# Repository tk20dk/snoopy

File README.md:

# snoopy
Three phase power meter

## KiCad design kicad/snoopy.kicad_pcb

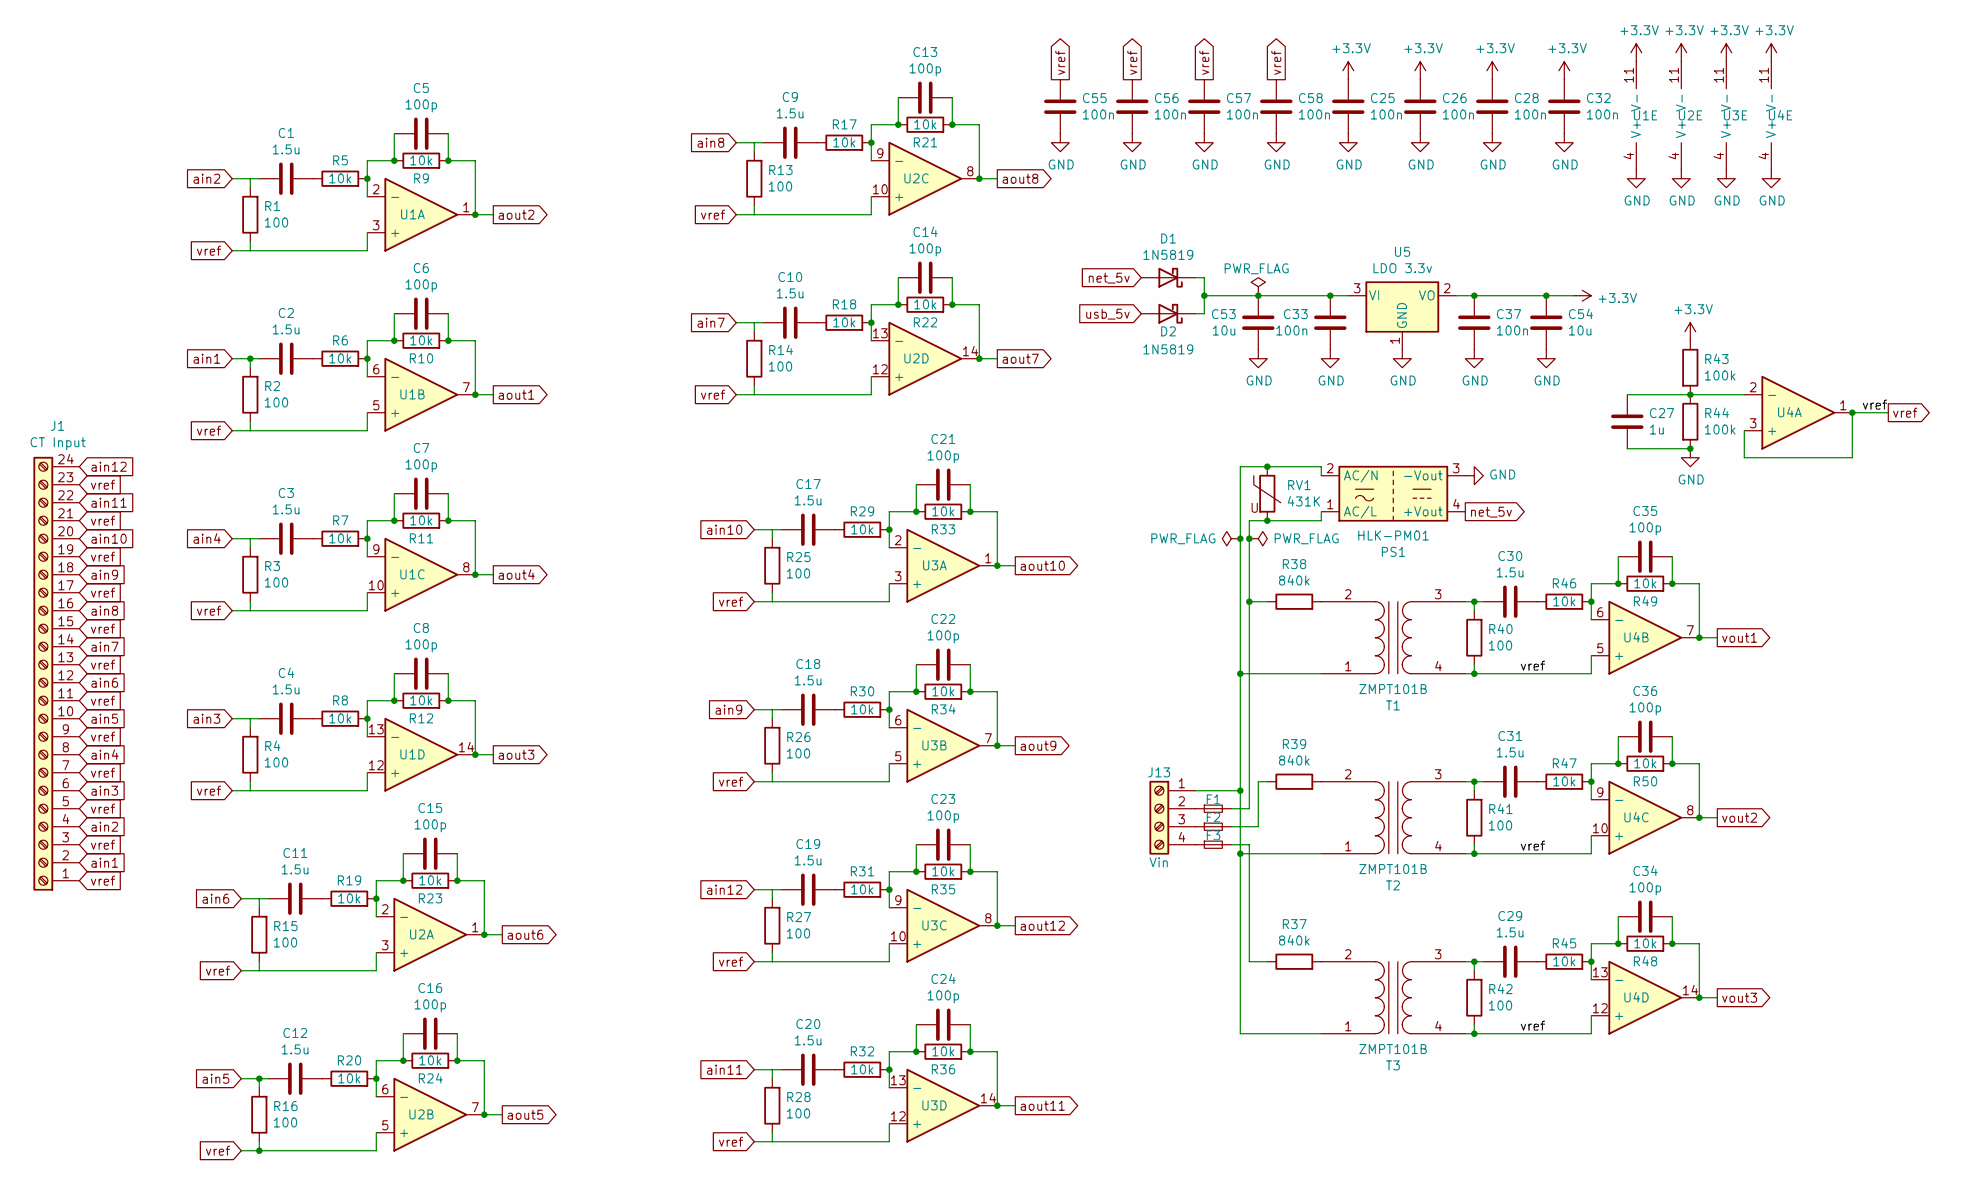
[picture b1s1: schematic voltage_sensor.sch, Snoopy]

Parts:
C1, C2, C3, C4, C9, C10, C11, C12, C17, C18, C19, C20, C29, C30, C31: 1.5u; C_0603_1608Metric
C5, C6, C7, C8, C13, C14, C15, C16, C21, C22, C23, C24, C34, C35, C36: 100p; C_0603_1608Metric
C25, C26, C28, C32, C33, C37, C55, C56, C57, C58: 100n; C_0603_1608Metric
C27: 1u; C_0603_1608Metric
C53, C54: 10u; C_0805_2012Metric
D1, D2: 1N5819; D_0805_2012Metric
F1, F2, F3: 500mA; Fuse_1206_3216Metric
J1: CT Input; TerminalBlock_1x24_P2.54mm_Horizontal
J13: Vin; TerminalBlock_bornier-4_P5.08mm
PS1: HLK-PM01; Converter_ACDC_HiLink_HLK-PMxx
R1, R2, R3, R4, R13, R14, R15, R16, R25, R26, R27, R28, R40, R41, R42: 100; R_0805_2012Metric
R5, R6, R7, R8, R9, R10, R11, R12, R17, R18, R19, R20, R21, R22, R23, R24, R29, R30, R31, R32, R33, R34, R35, R36, R45, R46, R47, R48, R49, R50: 10k; R_0603_1608Metric
R37, R38, R39: 840k; R_0805_2012Metric
R43, R44: 100k; R_0603_1608Metric
RV1: 431K; RV_Disc_D7mm_W3.7mm_P5mm
T1, T2, T3: ZMPT101B; Transformer_ZAPT101B
U1, U2, U3, U4: MCP604; SOIC-14_3.9x8.7mm_P1.27mm
U5: LDO 3.3v; SOT-223-3_TabPin2

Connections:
+3V3: C25.1, C26.1, C28.1, C32.1, C37.1, C54.1, R43.1, U1.11 (V-), U2.11 (V-), U3.11 (V-), U4.11 (V-), U5.2 (VO); also elsewhere on the board
GND: C25.2, C26.2, C27.2, C28.2, C32.2, C33.1, C37.2, C53.1, C54.2, C55.2, C56.2, C57.2, C58.2, PS1.3 (-Vout), R44.2, U1.4 (V+), U2.4 (V+), U3.4 (V+), U4.4 (V+), U5.1 (GND); also elsewhere on the board
unnamed: C1.2, R5.1
unnamed: C2.2, R6.1
unnamed: C3.2, R7.1
unnamed: C4.2, R8.1
unnamed: C5.2, R5.2, R9.1, U1.2 (-)
unnamed: C6.2, R6.2, R10.1, U1.6 (-)
unnamed: C7.2, R7.2, R11.1, U1.9 (-)
unnamed: C8.2, R8.2, R12.1, U1.13 (-)
unnamed: C9.2, R17.1
unnamed: C10.2, R18.1
unnamed: C11.2, R19.1
unnamed: C12.2, R20.1
unnamed: C13.2, R17.2, R21.1, U2.9 (-)
unnamed: C14.2, R18.2, R22.1, U2.13 (-)
unnamed: C15.2, R19.2, R23.1, U2.2 (-)
unnamed: C16.2, R20.2, R24.1, U2.6 (-)
unnamed: C17.2, R29.1
unnamed: C18.2, R30.1
unnamed: C19.2, R31.1
unnamed: C20.2, R32.1
unnamed: C21.2, R29.2, R33.1, U3.2 (-)
unnamed: C22.2, R30.2, R34.1, U3.6 (-)
unnamed: C23.2, R31.2, R35.1, U3.9 (-)
unnamed: C24.2, R32.2, R36.1, U3.13 (-)
unnamed: C27.1, R43.2, R44.1, U4.2 (-)
unnamed: C29.1, R42.2, T3.3 (SA)
unnamed: C29.2, R45.1
unnamed: C30.1, R40.2, T1.3 (SA)
unnamed: C30.2, R46.1
unnamed: C31.1, R41.2, T2.3 (SA)
unnamed: C31.2, R47.1
unnamed: C33.2, C53.2, D1.1 (K), D2.1 (K), U5.3 (VI)
unnamed: C34.2, R45.2, R48.1, U4.13 (-)
unnamed: C35.2, R46.2, R49.1, U4.6 (-)
unnamed: C36.2, R47.2, R50.1, U4.9 (-)
unnamed: F1.1, J13.2
unnamed: F1.2, PS1.1 (AC/L), R38.1, RV1.2
unnamed: F2.1, J13.3
unnamed: F2.2, R39.1
unnamed: F3.1, J13.4
unnamed: F3.2, R37.1
unnamed: J13.1, PS1.2 (AC/N), RV1.1, T1.1 (AA), T2.1 (AA), T3.1 (AA)
unnamed: R37.2, T3.2 (AB)
unnamed: R38.2, T1.2 (AB)
unnamed: R39.2, T2.2 (AB)
ain1: C2.1, J1.2, R2.2
ain2: C1.1, J1.4, R1.2
ain3: C4.1, J1.6, R4.2
ain4: C3.1, J1.8, R3.2
ain5: C12.1, J1.10, R16.2
ain6: C11.1, J1.12, R15.2
ain7: C10.1, J1.14, R14.2
ain8: C9.1, J1.16, R13.2
ain9: C18.1, J1.18, R26.2
ain10: C17.1, J1.20, R25.2
ain11: C20.1, J1.22, R28.2
ain12: C19.1, J1.24, R27.2
aout1: C6.1, R10.2, U1.7; also elsewhere on the board
aout2: C5.1, R9.2, U1.1; also elsewhere on the board
aout3: C8.1, R12.2, U1.14; also elsewhere on the board
aout4: C7.1, R11.2, U1.8; also elsewhere on the board
aout5: C16.1, R24.2, U2.7; also elsewhere on the board
aout6: C15.1, R23.2, U2.1; also elsewhere on the board
aout7: C14.1, R22.2, U2.14; also elsewhere on the board
aout8: C13.1, R21.2, U2.8; also elsewhere on the board
aout9: C22.1, R34.2, U3.7; also elsewhere on the board
aout10: C21.1, R33.2, U3.1; also elsewhere on the board
aout11: C24.1, R36.2, U3.14; also elsewhere on the board
aout12: C23.1, R35.2, U3.8; also elsewhere on the board
net_5v: D1.2 (A), PS1.4 (+Vout)
usb_5v: D2.2 (A); also elsewhere on the board
vout1: C35.1, R49.2, U4.7; also elsewhere on the board
vout2: C36.1, R50.2, U4.8; also elsewhere on the board
vout3: C34.1, R48.2, U4.14; also elsewhere on the board
vref: C55.1, C56.1, C57.1, C58.1, J1.1, J1.3, J1.5, J1.7, J1.9, J1.11, J1.13, J1.15, J1.17, J1.19, J1.21, J1.23, R1.1, R2.1, R3.1, R4.1, R13.1, R14.1, R15.1, R16.1, R25.1, R26.1, R27.1, R28.1, R40.1, R41.1, R42.1, T1.4 (SB), T2.4 (SB), T3.4 (SB), U1.3 (+), U1.5 (+), U1.10 (+), U1.12 (+), U2.3 (+), U2.5 (+), U2.10 (+), U2.12 (+), U3.3 (+), U3.5 (+), U3.10 (+), U3.12 (+), U4.1, U4.3 (+), U4.5 (+), U4.10 (+), U4.12 (+); also elsewhere on the board

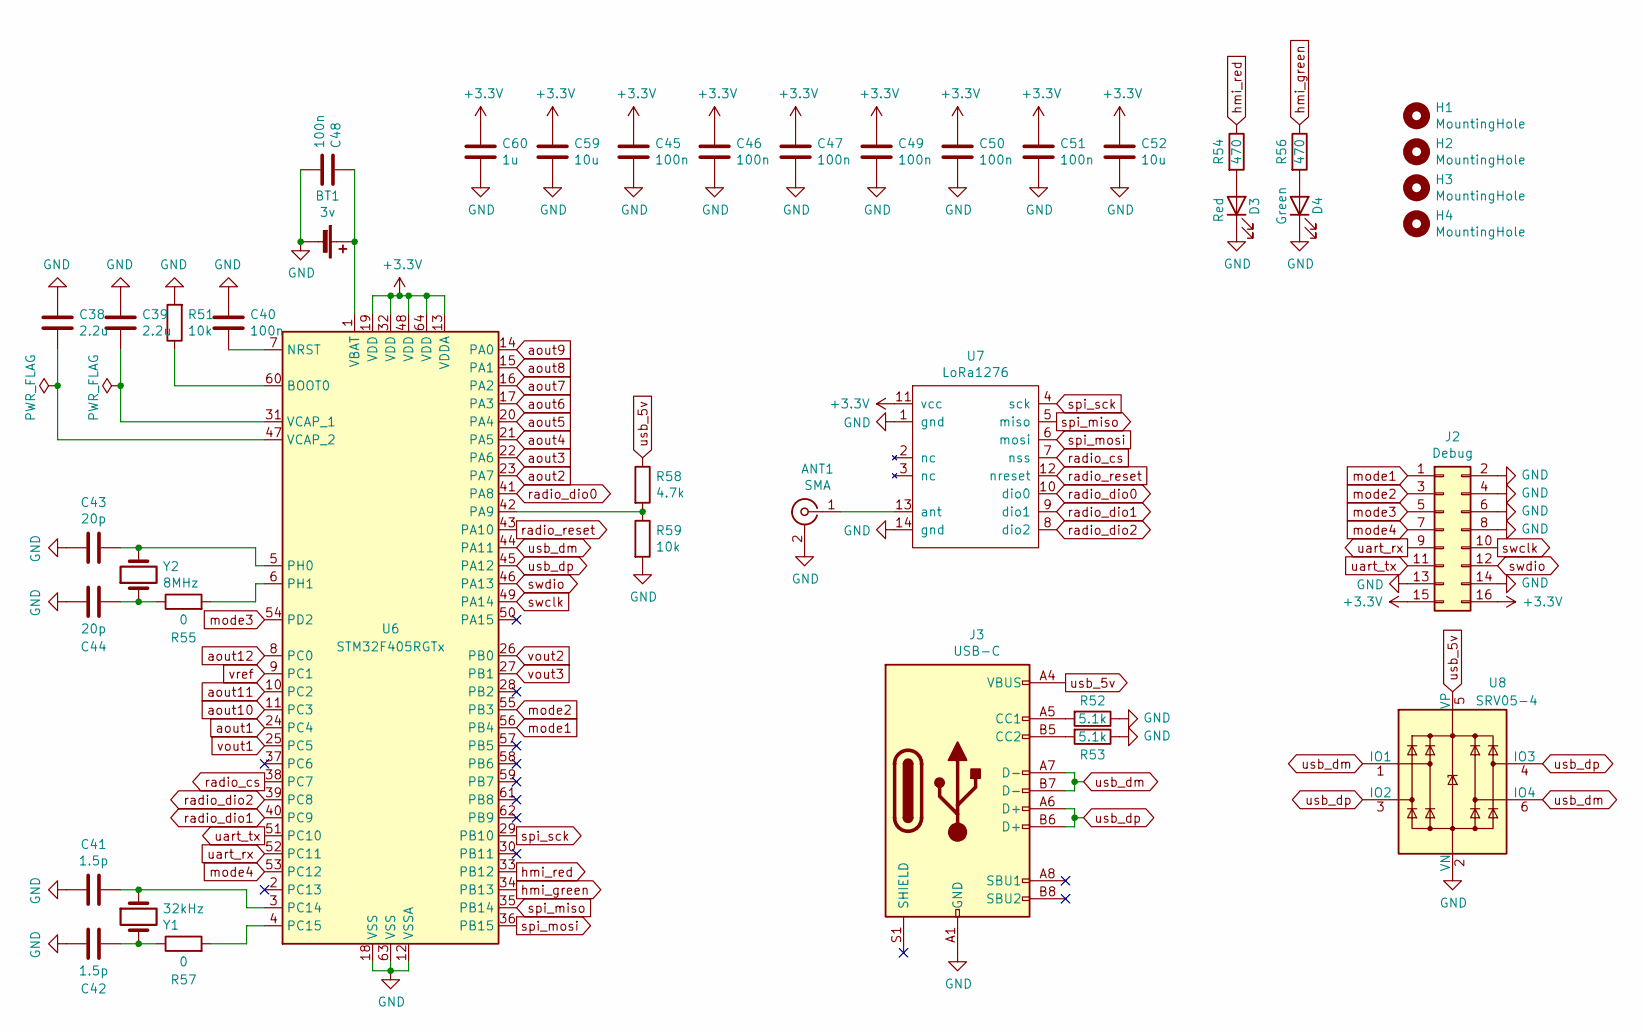
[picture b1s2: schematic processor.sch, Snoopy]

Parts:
ANT1: SMA; SMA_Molex_73251-2200_Horizontal
BT1: 3v; Battery_Panasonic_CR1220-VCN_Vertical_CircularHoles
C38, C39: 2.2u; C_0805_2012Metric
C40, C45, C46, C47, C48, C49, C50, C51: 100n; C_0603_1608Metric
C41, C42: 1.5p; C_0603_1608Metric
C43, C44: 20p; C_0603_1608Metric
C52, C59: 10u; C_0805_2012Metric
C60: 1u; C_0603_1608Metric
D3: Red; LED_0603_1608Metric
D4: Green; LED_0603_1608Metric
H1, H2, H3, H4: MountingHole; MountingHole_3mm
J2: Debug; PinHeader_2x08_P2.54mm_Vertical
J3: USB-C; USB_C_Receptacle_HRO_TYPE-C-31-M-12
R51, R59: 10k; R_0603_1608Metric
R52, R53: 5.1k; R_0603_1608Metric
R54, R56: 470; R_0603_1608Metric
R55, R57: 0; R_0603_1608Metric
R58: 4.7k; R_0603_1608Metric
U6: STM32F405RGTx; LQFP-64_10x10mm_P0.5mm
U7: LoRa1276; NicerRF-LoRa1276
U8: SRV05-4; SOT-23-6
Y1: 32kHz; Crystal_DS26_D2.0mm_L6.0mm_Horizontal
Y2: 8MHz; Crystal_SMD_HC49-SD

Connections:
+3V3: C45.1, C46.1, C47.1, C49.1, C50.1, C51.1, C52.1, C59.1, C60.1, J2.15, J2.16, U6.13 (VDDA), U6.19 (VDD), U6.32 (VDD), U6.48 (VDD), U6.64 (VDD), U7.11 (vcc); also elsewhere on the board
GND: ANT1.2 (Ext), BT1.2 (-), C38.1, C39.1, C40.1, C41.2, C42.2, C43.2, C44.2, C45.2, C46.2, C47.2, C48.2, C49.2, C50.2, C51.2, C52.2, C59.2, C60.2, D3.1 (K), D4.1 (K), J2.2, J2.4, J2.6, J2.8, J2.13, J2.14, J3.A1 (GND), J3.A12 (GND), J3.B1 (GND), J3.B12 (GND), R51.2, R52.1, R53.1, R59.2, U6.12 (VSSA), U6.18 (VSS), U6.63 (VSS), U7.1 (gnd), U7.14 (gnd), U8.2 (VN); also elsewhere on the board
unnamed: ANT1.1 (In), U7.13 (ant)
unnamed: BT1.1 (+), C48.1, U6.1 (VBAT)
unnamed: C38.2, U6.47 (VCAP_2)
unnamed: C39.2, U6.31 (VCAP_1)
unnamed: C40.2, U6.7 (NRST)
unnamed: C41.1, U6.3 (PC14), Y1.1
unnamed: C42.1, R57.1, Y1.2
unnamed: C43.1, U6.5 (PH0), Y2.2
unnamed: C44.1, R55.1, Y2.1
unnamed: D3.2 (A), R54.2
unnamed: D4.2 (A), R56.2
unnamed: J3.A5 (CC1), R52.2
unnamed: J3.B5 (CC2), R53.2
unnamed: R51.1, U6.60 (BOOT0)
unnamed: R55.2, U6.6 (PH1)
unnamed: R57.2, U6.4 (PC15)
unnamed: R58.2, R59.1, U6.42 (PA9)
aout1: U6.24 (PC4); also elsewhere on the board
aout2: U6.23 (PA7); also elsewhere on the board
aout3: U6.22 (PA6); also elsewhere on the board
aout4: U6.21 (PA5); also elsewhere on the board
aout5: U6.20 (PA4); also elsewhere on the board
aout6: U6.17 (PA3); also elsewhere on the board
aout7: U6.16 (PA2); also elsewhere on the board
aout8: U6.15 (PA1); also elsewhere on the board
aout9: U6.14 (PA0); also elsewhere on the board
aout10: U6.11 (PC3); also elsewhere on the board
aout11: U6.10 (PC2); also elsewhere on the board
aout12: U6.8 (PC0); also elsewhere on the board
hmi_green: R56.1, U6.34 (PB13)
hmi_red: R54.1, U6.33 (PB12)
mode1: J2.1, U6.56 (PB4)
mode2: J2.3, U6.55 (PB3)
mode3: J2.5, U6.54 (PD2)
mode4: J2.7, U6.53 (PC12)
radio_cs: U6.38 (PC7), U7.7 (nss)
radio_dio0: U6.41 (PA8), U7.10 (dio0)
radio_dio1: U6.40 (PC9), U7.9 (dio1)
radio_dio2: U6.39 (PC8), U7.8 (dio2)
radio_reset: U6.43 (PA10), U7.12 (nreset)
spi_miso: U6.35 (PB14), U7.5 (miso)
spi_mosi: U6.36 (PB15), U7.6 (mosi)
spi_sck: U6.29 (PB10), U7.4 (sck)
swclk: J2.10, U6.49 (PA14)
swdio: J2.12, U6.46 (PA13)
uart_rx: J2.9, U6.52 (PC11)
uart_tx: J2.11, U6.51 (PC10)
usb_5v: J3.A4 (VBUS), J3.A9 (VBUS), J3.B4 (VBUS), J3.B9 (VBUS), R58.1, U8.5 (VP); also elsewhere on the board
usb_dm: J3.A7 (D-), J3.B7 (D-), U6.44 (PA11), U8.1 (IO1), U8.6 (IO4)
usb_dp: J3.A6 (D+), J3.B6 (D+), U6.45 (PA12), U8.3 (IO2), U8.4 (IO3)
vout1: U6.25 (PC5); also elsewhere on the board
vout2: U6.26 (PB0); also elsewhere on the board
vout3: U6.27 (PB1); also elsewhere on the board
vref: U6.9 (PC1); also elsewhere on the board

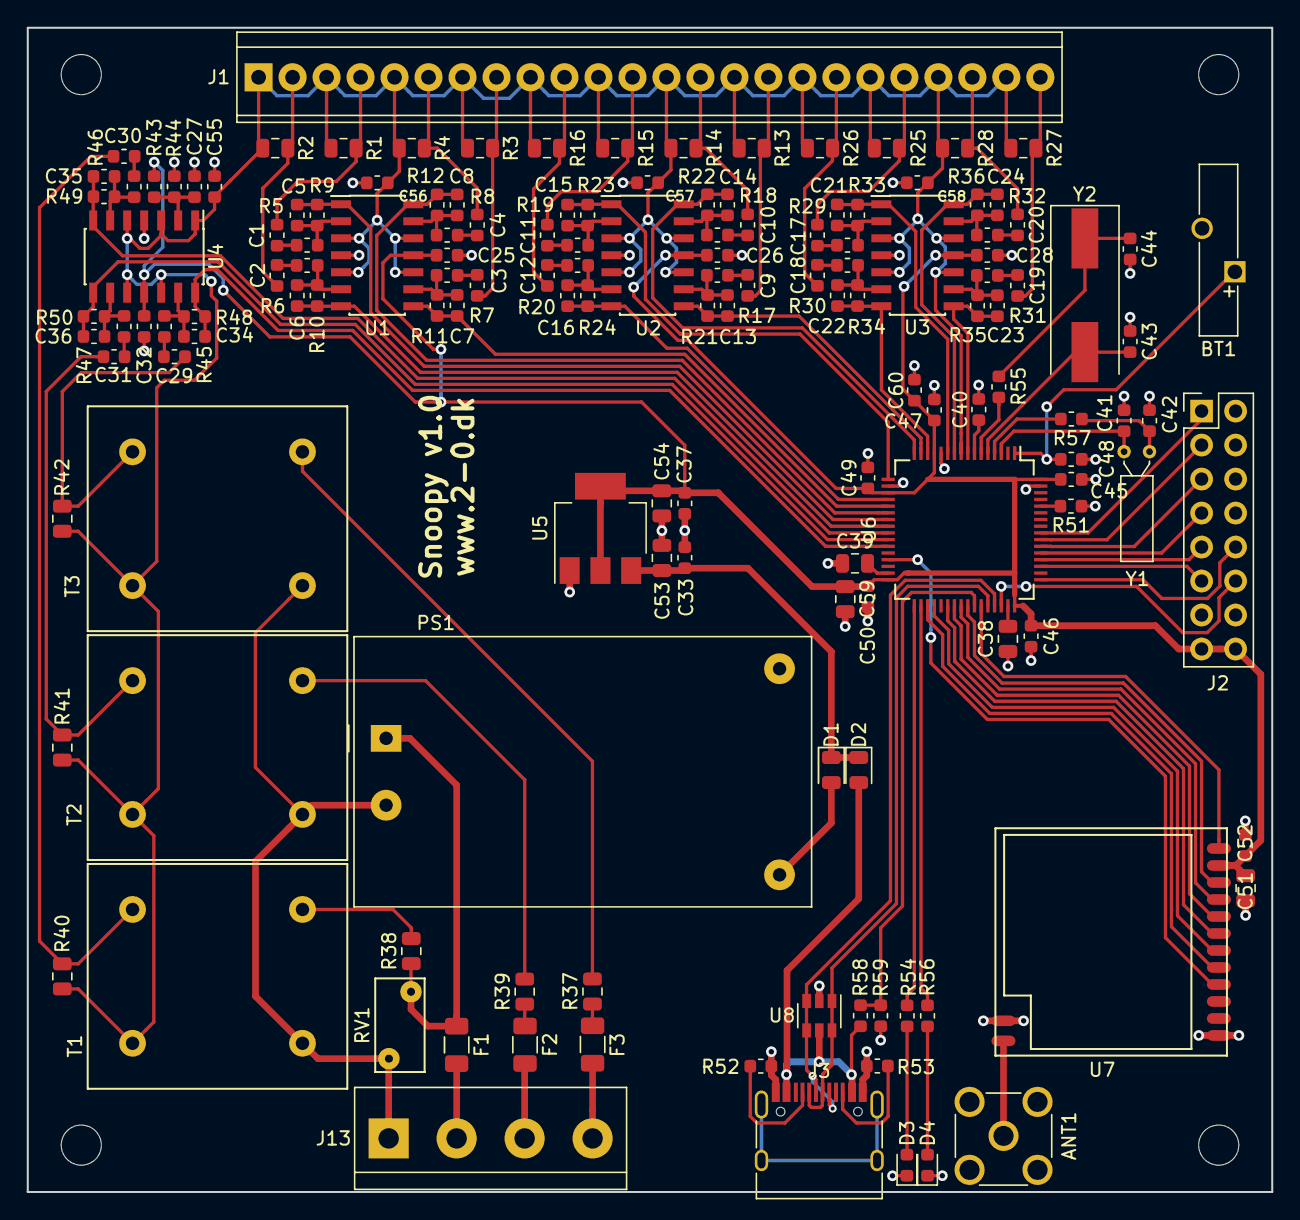
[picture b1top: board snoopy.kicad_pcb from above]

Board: 2 copper layers, 93.0 x 87.0 mm, 151 parts (0 on the bottom side), 114 nets.

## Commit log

2020-11-25 created initial pcb
2020-11-25 removed hg repository
